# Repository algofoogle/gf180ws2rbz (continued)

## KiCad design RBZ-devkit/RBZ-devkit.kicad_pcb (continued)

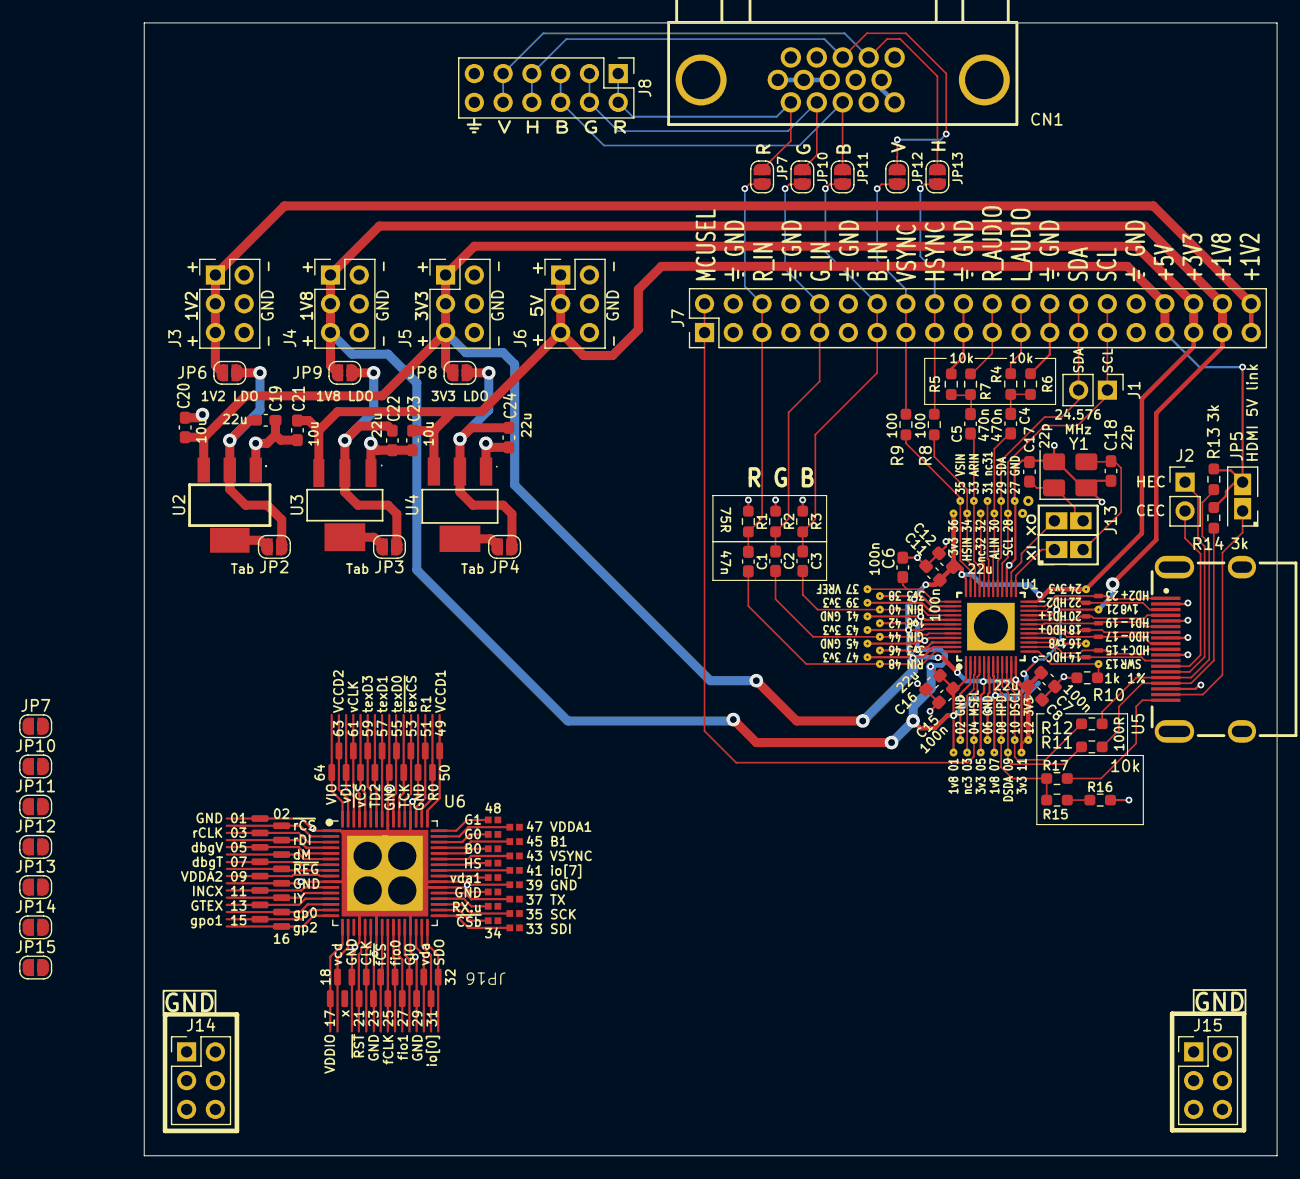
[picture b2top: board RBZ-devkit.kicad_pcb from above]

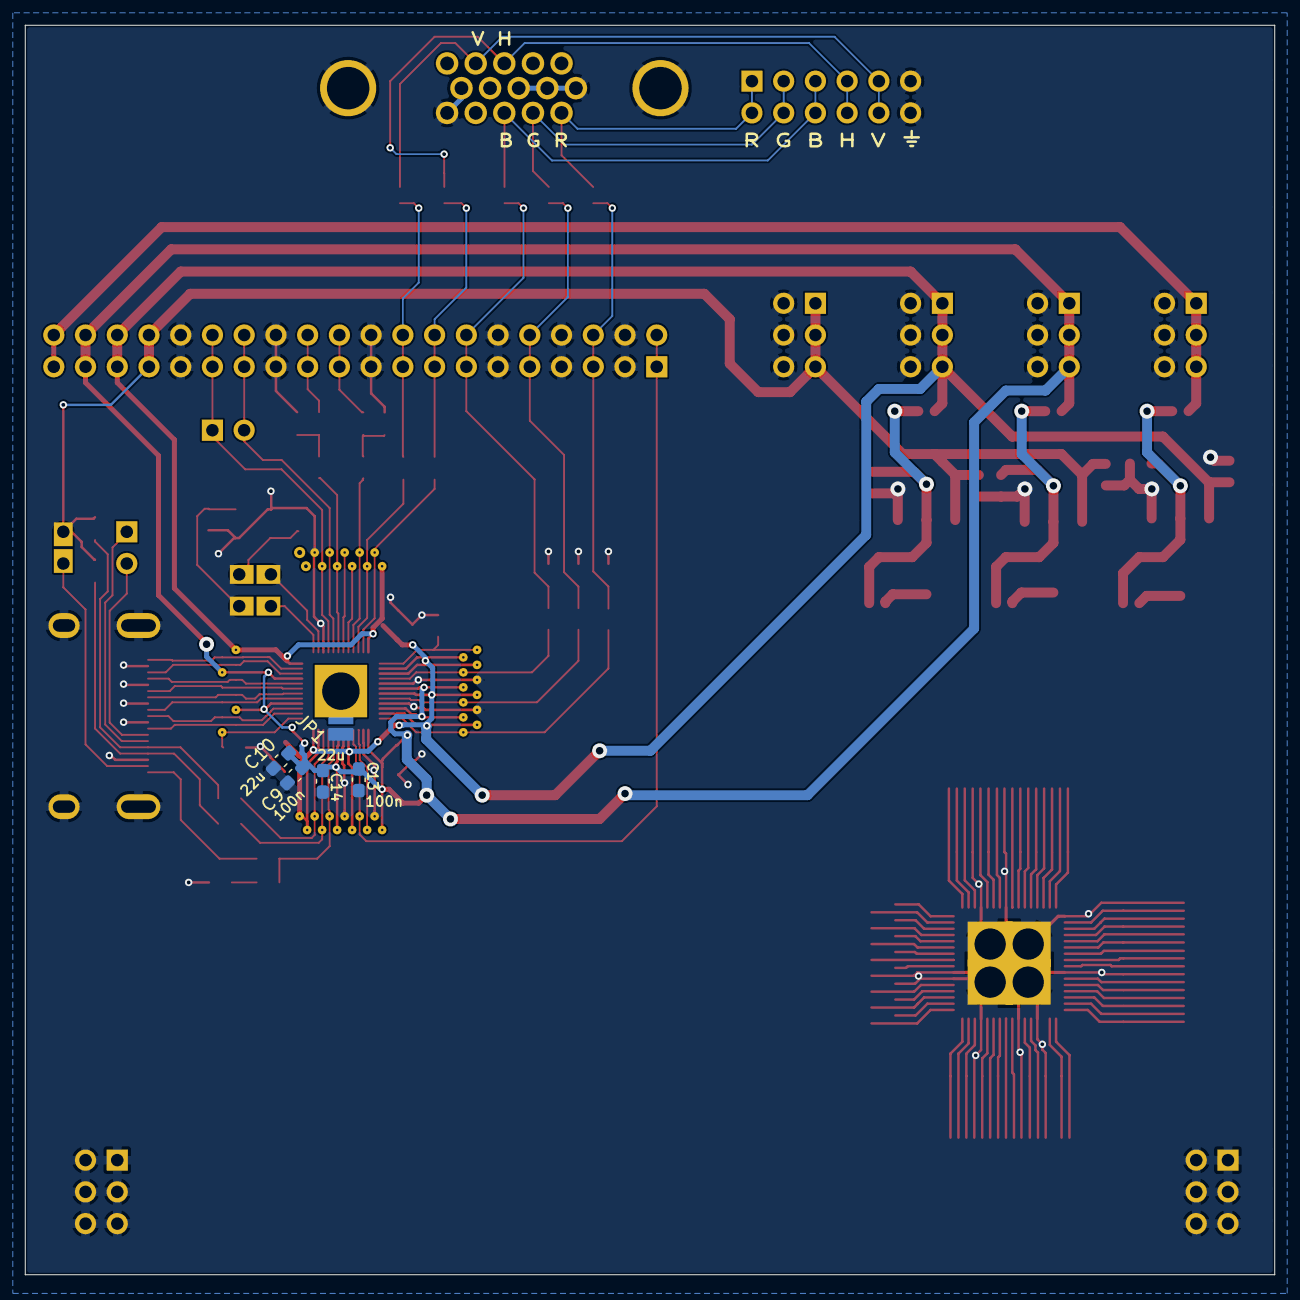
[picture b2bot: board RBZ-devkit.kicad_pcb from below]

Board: 2 copper layers, 100.0 x 100.0 mm, 88 parts (5 on the bottom side), 115 nets.

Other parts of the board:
JP7#2: vccd; SolderJumper-2_P1.3mm_Open_RoundedPad1.0x1.5mm
JP10#2: vccd1; SolderJumper-2_P1.3mm_Open_RoundedPad1.0x1.5mm
JP11#2: vccd2; SolderJumper-2_P1.3mm_Open_RoundedPad1.0x1.5mm
JP12#2, JP13#2: SolderJumper-2_P1.3mm_Open_RoundedPad1.0x1.5mm

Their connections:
+5V: JP7#2.2 (B), JP10#2.2 (B), JP11#2.2 (B); also elsewhere on the board
/HSYNC: JP13#2.2 (B); also elsewhere on the board
/VGA_HSYNC: JP12#2.1 (A); also elsewhere on the board
/VGA_VSYNC: JP13#2.1 (A); also elsewhere on the board
/VSYNC: JP12#2.2 (B); also elsewhere on the board
/vccd: JP7#2.1 (A); also elsewhere on the board
/vccd1: JP10#2.1 (A); also elsewhere on the board
/vccd2: JP11#2.1 (A); also elsewhere on the board

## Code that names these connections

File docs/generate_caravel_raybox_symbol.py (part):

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        "RBZ I/O",
        (
            # View-vector SPI slave: io[24:22].
            pin(60, "vec_cs_n/io[22]", "input", "left", shape="inverted"),
            pin(61, "vec_sclk/io[23]", "input", "left", shape="clock"),
            pin(62, "vec_mosi/io[24]", "input", "left"),
            # Register SPI slave: io[27:25].
            pin(2, "reg_cs_n/io[25]", "input", "left", 1, "inverted"),
            pin(3, "reg_sclk/io[26]", "input", "left", shape="clock"),
            pin(4, "reg_mosi/io[27]", "input", "left"),
            # Debug controls: io[30:28].
            pin(5, "debug_vec/io[28]", "input", "left", 1),
            pin(6, "debug_map/io[29]", "input", "left"),
            pin(7, "debug_trace/io[30]", "input", "left"),
            # Active-low registered-output enable: io[31].
            pin(8, "reg_outs_enb/io[31]", "input", "left", 1, "inverted"),
            # Demo mode controls: io[34:32].
            pin(11, "mode0_inc_px/io[32]", "input", "left", 1),
            pin(12, "mode1_inc_py/io[33]", "input", "left"),
            pin(13, "mode2_gen_tex/io[34]", "input", "left"),
            # VGA: io[15:8].
            pin(42, "hsync_n/io[8]", "output", "right", shape="inverted"),
            pin(43, "vsync_n/io[9]", "output", "right", shape="inverted"),
            pin(44, "rgb[0]/io[10]", "output", "right"),
            pin(45, "rgb[1]/io[11]", "output", "right"),
            pin(46, "rgb[2]/io[12]", "output", "right"),
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            pin(51, "rgb[5]/io[15]", "output", "right"),
            # Texture QSPI master: io[21:16].  Keep the bus together even
            # though its individual pins have different directions.
            pin(53, "tex_cs_n/io[16]", "output", "right", 1, "inverted"),
            pin(54, "tex_sclk/io[17]", "output", "right"),
            pin(55, "tex_io0/io[18]", "bidirectional", "right"),
            pin(57, "tex_io1/io[19]", "input", "right"),
            pin(58, "tex_io2/io[20]", "input", "right"),
            pin(59, "tex_io3/io[21]", "input", "right"),
            # General-purpose diagnostic outputs: io[37:35].
            pin(14, "gpout[0]/io[35]", "output", "right", 1),
            pin(15, "gpout[1]/io[36]", "output", "right"),
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        (
            # Housekeeping: io[4:0], kept together on one side.
            pin(31, "jtag/io[0]", "input", "left"),
            pin(32, "hk_sdo/miso/io[1]", "output", "left"),
            pin(33, "hk_sdi/mosi/io[2]", "input", "left"),
            pin(34, "hk_csb/cs_n/io[3]", "input", "left", shape="inverted"),
            pin(35, "hk_sck/io[4]", "input", "left", shape="clock"),
            # Management serial/reset overlays: io[6:5].
            pin(36, "opt_user_reset/ser_rx/io[5]", "input", "left", 1),
            pin(37, "ser_tx/io[6]", "output", "left"),
            # Management interrupt: io[7].
            pin(41, "irq/io[7]", "input", "left", 1),
            # Package reset and shared system clock, at the top right.
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            pin(22, "system_clk", "input", "right", shape="clock"),
            # Dedicated management firmware-flash pins 24..27.  In this
            # implementation IO0 is always MOSI/output and IO1 MISO/input.
            pin(24, "flash_csb", "output", "right", 1, "inverted"),
            pin(25, "flash_clk", "output", "right"),
            pin(26, "flash_io0/mosi", "output", "right"),
            pin(27, "flash_io1/miso", "input", "right"),
            # Standalone management GPIO.
            pin(28, "gpio", "bidirectional", "right", 1),
        ),
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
